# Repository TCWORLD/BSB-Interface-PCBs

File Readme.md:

# Boiler System Bus (BSB) Interface PCB Designs

This repository contains a series of PCB designs used to interface between the Boiler System Bus (BSB) of certain heating systems and network interfaces.

## MCU Software

The hardware is compatible with the ESP32 software implementations from [fredlcore/BSB-LAN](https://github.com/fredlcore/BSB-LAN/). 
Note: This repo is **not affiliated** with said project in any way - support queries for these PCB designs should **not** be directed to that project.

## Hardware

The hardware is based around an ESP32 controller, with either PoE LAN or WiFi network connectivity.

The PCBs have been laid out using Eagle PCB V6.6 and use predominantly surface mount components to make machine assembly easier. Parts used are all available for assembly in JLCPCBs parts catalogue.

A library file containing all parts used is included in the repository.

CAM files are included for generating 2-Layer and 4-Layer Gerber files using a naming scheme compatible with JLCs upload.

The repository contains a ULP file that can be run to generate the CPL/BOM files for upload to JLC. 
The `LCSC_PART` and `JLC_X/Y/ROTATION` attributes have been added for each component to simplify generation of the assembly spreadsheets required by JLC. If changing the PCB designs, ensure these attributes are updated as necessary.

### BSB-to-PoELaN for DIN Mount enclosure

A full implementation including ESP32 WROOM-32UE controller, PoE Ethernet power and networking, and USB programming and SD card interfaces.

This design has been built and is fully functional. It requires the following settings in the BSB-LAN software:

* In `BSB_LAN_config.h`: Configure the following setting:
    ```
    byte bus_pins[2] = {36,4};
    ```
* In `BSB_LAN_custom_setup.h`: Add the following code:
    ```
    // Set TX Enable pin to output and set high now that the system is initialised and the
    // TX line is being driven correctly
    pinMode(32, OUTPUT);
    digitalWrite(32, HIGH);
    ```

The board and components have been designed for use with JLCPCBs economic assembly process. 

The form factor of the board has been designed to fit in a Camdenboss CNMB/3/KIT DIN mount enclosure to provide a tidy fully enclosed solution.

### BSB-to-UEXT Daughter Board *UNTESTED*

Designed to work with the ESP32-POE-ISO controller from Olimex, connecting vial the UEXT headers.

The PCB schematic is simply based on the design found at in the GitHub repository [fredlcore/BSB-LAN](https://github.com/fredlcore/BSB-LAN/tree/master/BSB_LAN/schematics).

There are some slight adaptions to provide ESD protection for the isolated B2B interface and designed to be surface-mount machine for machine assembly. 

### BSB-to-WiFi for DIN Mount enclosure *UNTESTED*

A full implementation including ESP32 WROOM-32E controller, WiFi-only networking (PCB antenna, footprint compatible with external antenna), and USB programming and SD card interfaces.
This variant omits the LAN components to reduce the number of parts and make the board cheaper to manufacture. 
Power is supplied from either a 12V screw terminal (isolated through DC/DC for safety), or powered by the USB programming port.

The board and components have been designed for use with JLCPCBs economic assembly process. 

The form factor of the board has been designed to fit in a Camdenboss CNMB/2/KIT DIN mount enclosure to provide a tidy fully enclosed solution.

---

<br />This work is licensed under a <a rel="license" href="http://creativecommons.org/licenses/by-nc-sa/4.0/">Creative Commons Attribution-NonCommercial-ShareAlike 4.0 International License</a>.

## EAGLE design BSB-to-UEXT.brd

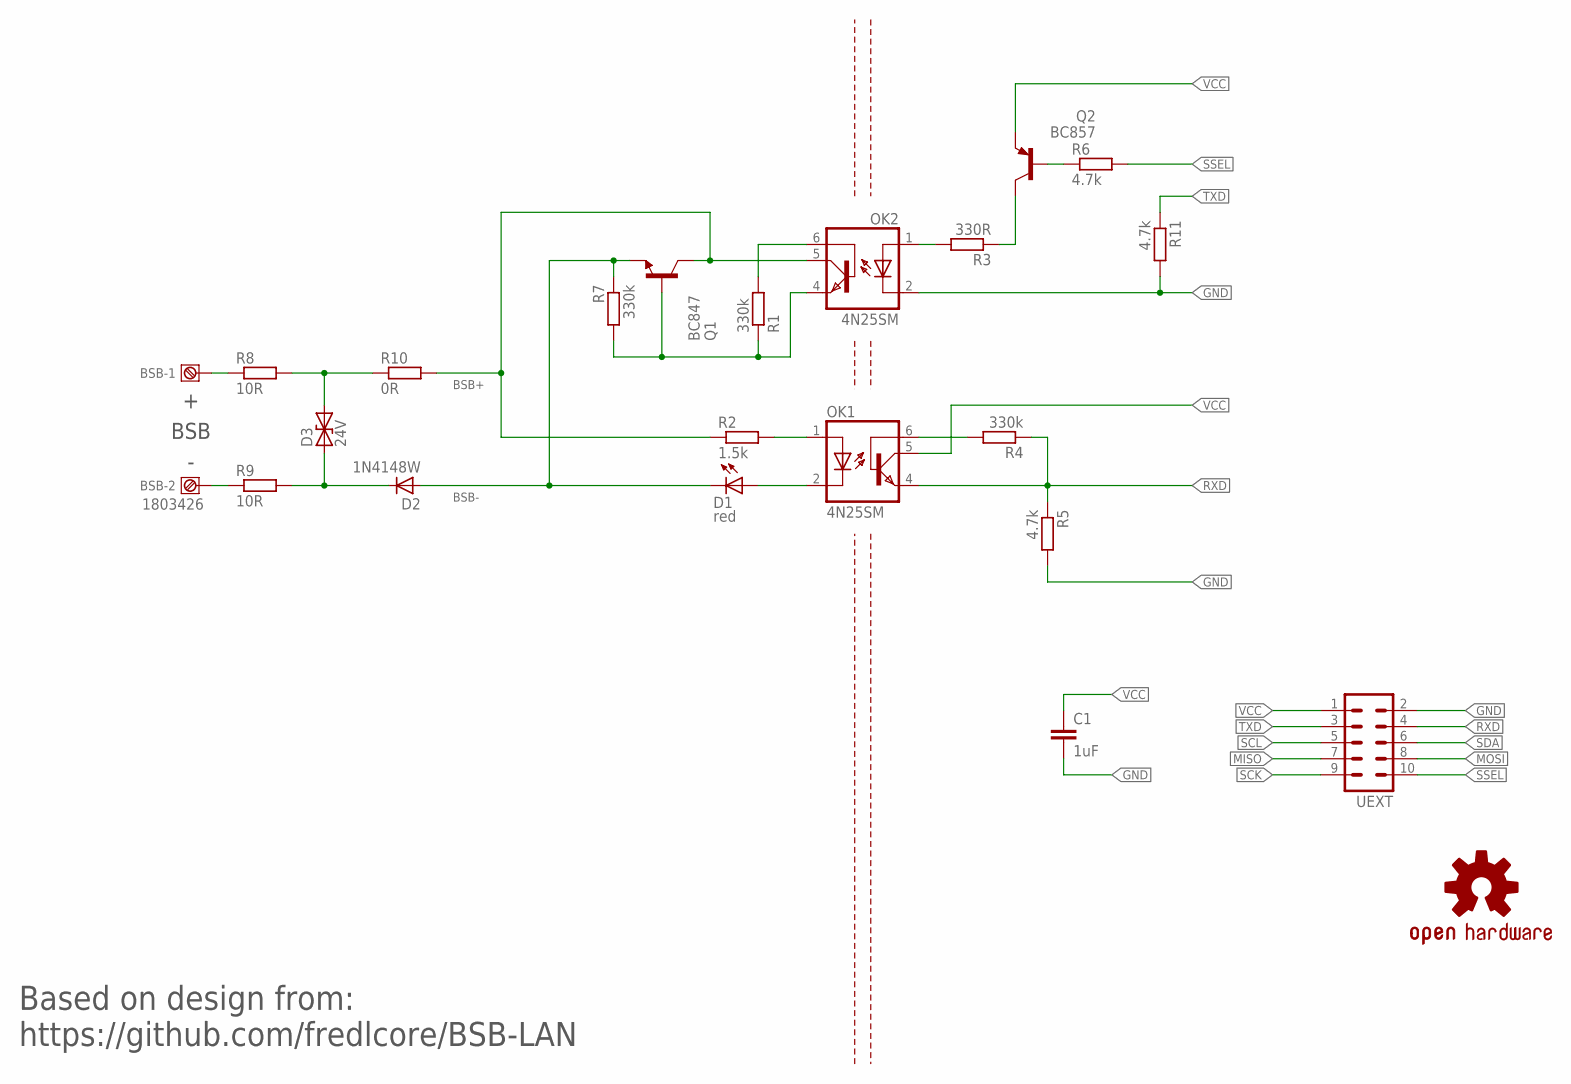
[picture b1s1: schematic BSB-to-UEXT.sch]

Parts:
BSB: 1803426; LCSC_PART C480514
C1: 1uF; C0805; LCSC_PART C28323
D1: red; CHIPLED_0805; LCSC_PART C84256
D2: 1N4148W; SOD123; LCSC_PART C81598
D3: 24V; SMBG; LCSC_PART C83268
OK1, OK2: 4N25SM; DIL6-SMD; LCSC_PART C258246
Q1: BC847; SOT23; LCSC_PART C130417
Q2: BC857; SOT23-BEC; LCSC_PART C426782
R1, R4, R7: 330k; R0805; LCSC_PART C17629
R2: 1.5k; R0805; LCSC_PART C4310
R3: 330R; R0805; LCSC_PART C17630
R5, R6, R11: 4.7k; R0805; LCSC_PART C17673
R8, R9: 10R; R1206; LCSC_PART C17903
R10: 0R; R1206L; LCSC_PART C17888
U$3: DNI; OSHW-LOGO-M
UEXT: ML10F

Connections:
BSB+: OK2.5 (COL), Q1.3 (C), R2.1, R10.2
BSB-: D1.C, D2.A, Q1.2 (E), R7.1
BSB-RX-A: OK1.1 (A), R2.2
BSB-RX-K: D1.A, OK1.2 (C)
BSB-TX-B: OK2.6 (BAS), R1.2
BSB-TX-E: OK2.4 (EMI), Q1.1 (B), R1.1, R7.2
CON-BSB+: BSB.1, R8.1
CON-BSB-: BSB.2, R9.1
GND: C1.2, OK2.2 (C), R5.2, R11.2, UEXT.2
MISO: UEXT.7
MOSI: UEXT.8
RXD: OK1.4 (EMI), R4.1, R5.1, UEXT.4
RXD-B: OK1.6 (BAS), R4.2
SCK: UEXT.9
SCL: UEXT.5
SDA: UEXT.6
SSEL: R6.2, UEXT.10
TVS-BSB+: D3.2, R8.2, R10.1
TVS-BSB-: D2.C, D3.1, R9.2
TXD: R11.1, UEXT.3
TXD-A: OK2.1 (A), R3.2
TXD-B: Q2.B, R6.1
TXD-C: Q2.C, R3.1
VCC: C1.1, OK1.5 (COL), Q2.E, UEXT.1

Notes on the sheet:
+ BSB -
Based on design from: https://github.com/fredlcore/BSB-LAN

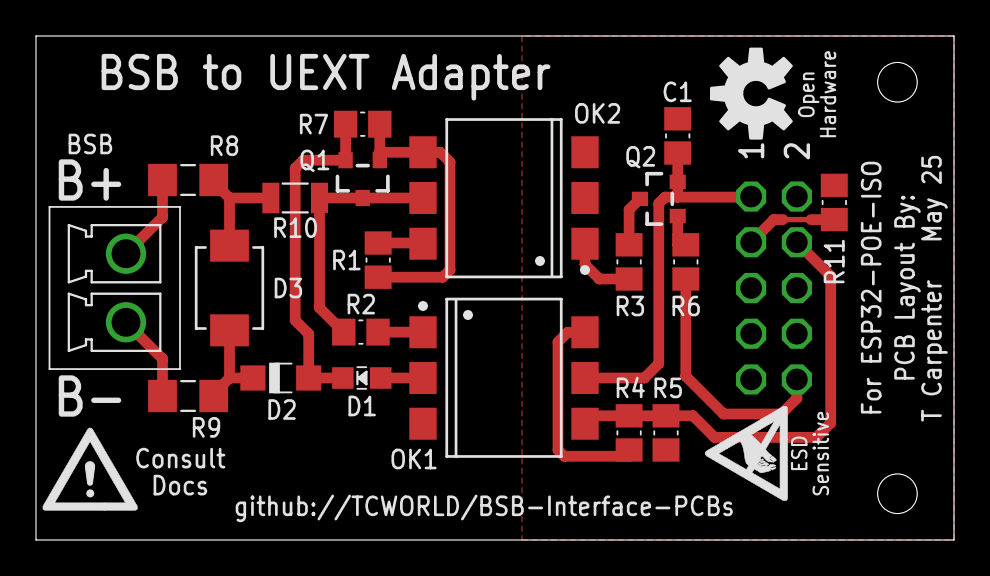
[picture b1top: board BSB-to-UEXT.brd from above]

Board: 2 copper layers, 51.0 x 28.0 mm, 24 parts (1 on the bottom side), 19 nets.

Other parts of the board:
U$1: WARN-TINY
U$2: ESD-TINY

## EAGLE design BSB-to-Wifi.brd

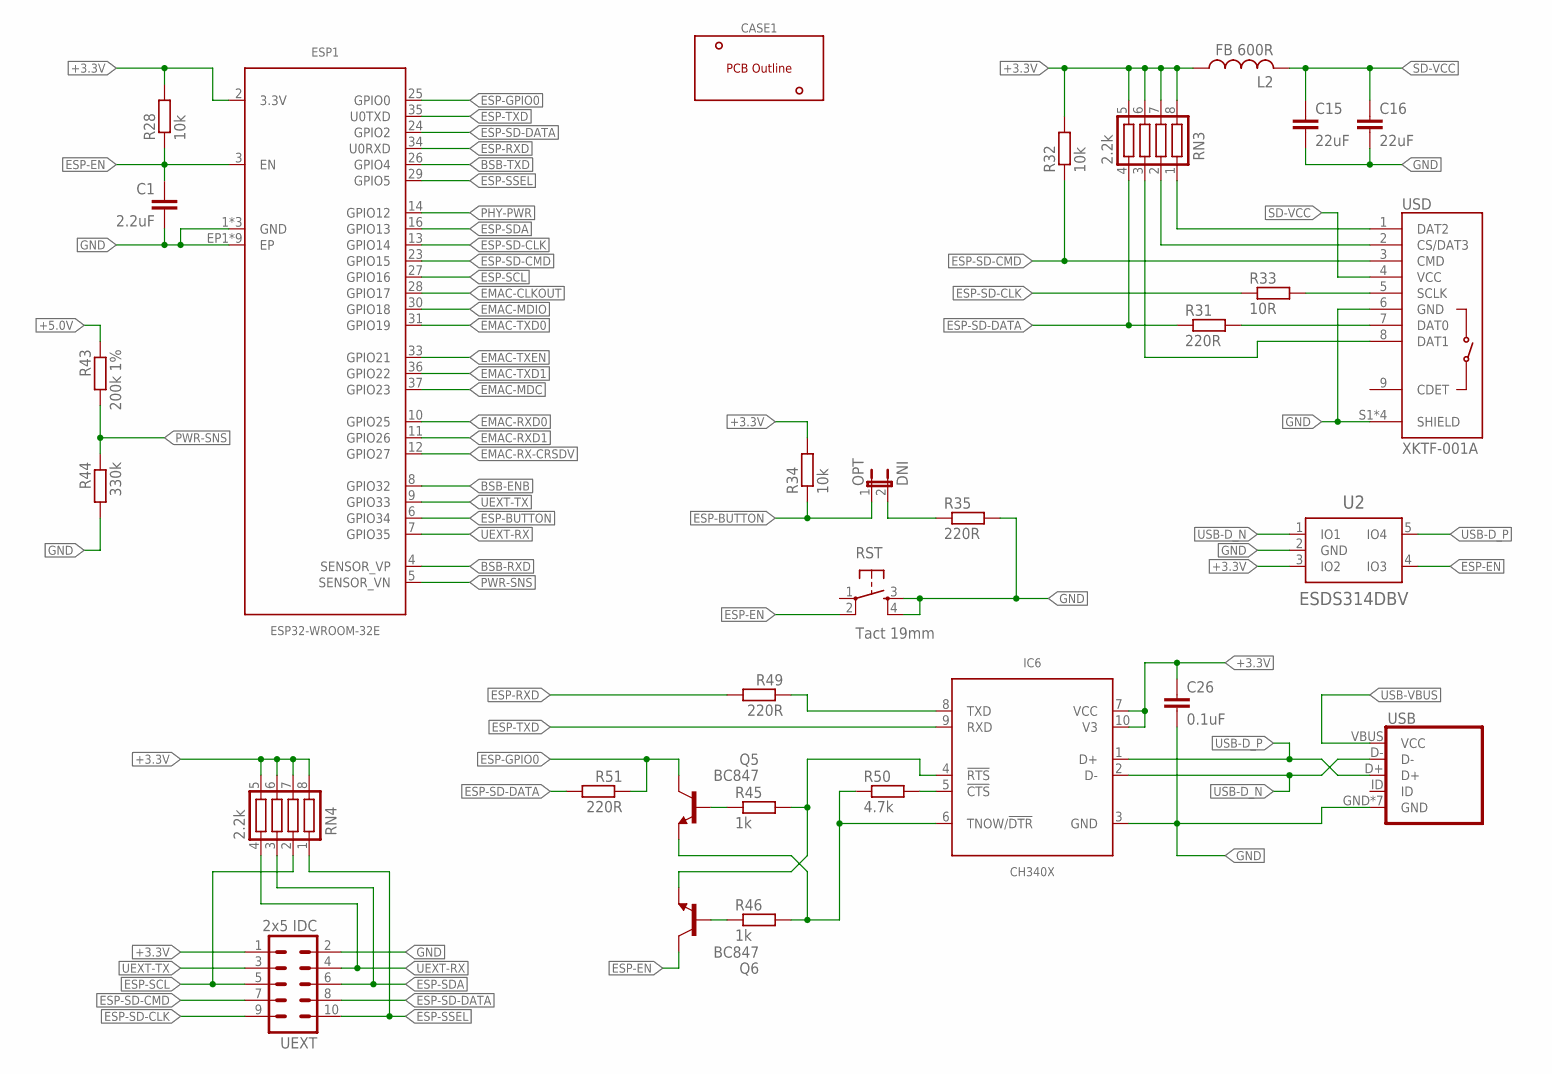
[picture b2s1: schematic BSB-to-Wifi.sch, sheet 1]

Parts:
C1: 2.2uF; C0603; LCSC_PART C23630
C15, C16: 22uF; C0805L; LCSC_PART C45783
C26: 0.1uF; C0402; LCSC_PART C1525
CASE1: DNI; CNMB/2-
ESP1: ESP32-WROOM-32E
IC6: CH340X; MSOP10
L2: FB 600R; L2010; LCSC_PART C1017
OPT: DNI; 1X02
Q5: BC847; SOT23; LCSC_PART C130417
Q6: BC847; SOT23
R28, R32, R34: 10k; R0402; LCSC_PART C25744
R31, R35, R49, R51: 220R; R0402; LCSC_PART C25091
R33: 10R; R0603L; LCSC_PART C22859
R43: 200k 1%; R0402; LCSC_PART C25764
R44: 330k; R0603L; LCSC_PART C23137
R45, R46: 1k; R0402; LCSC_PART C11702
R50: 4.7k; R0402; LCSC_PART C25900
RN3, RN4: 2.2k; CTS742C083; LCSC_PART C414564
RST: Tact 19mm; TACTILE_SWITCH; LCSC_PART C2837529
U2: ESDS314DBV; DBV0005A-SOT23
UEXT: 2x5 IDC; ML10
USB: ZX62-B-5PA(33); USB-MICROB
USD: XKTF-001A; MICRO-SD

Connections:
+3.3V: C26.1, ESP1.2 (3.3V), IC6.7 (VCC), IC6.10 (V3), L2.1, R28.2, R32.2, R34.2, RN3.5, RN3.6, RN3.7, RN3.8, RN4.5, RN4.6, RN4.7, RN4.8, U2.3 (IO2), UEXT.1; also elsewhere on the board
+5.0V: R43.1; also elsewhere on the board
BSB-ENB: ESP1.8 (GPIO32); also elsewhere on the board
BSB-RXD: ESP1.4 (SENSOR_VP); also elsewhere on the board
BSB-TXD: ESP1.26 (GPIO4); also elsewhere on the board
CH340-!CTS: IC6.5 (!CTS), R50.2
CH340-!DTR: IC6.6 (TNOW/!DTR), Q5.2 (E), R46.2, R50.1
CH340-!RTS: IC6.4 (!RTS), Q6.2 (E), R45.2
CH340-TXD: IC6.8 (TXD), R49.1
EMAC-CLKOUT: ESP1.28 (GPIO17)
EMAC-MDC: ESP1.37 (GPIO23)
EMAC-MDIO: ESP1.30 (GPIO18)
EMAC-RX-CRSDV: ESP1.12 (GPIO27)
EMAC-RXD0: ESP1.10 (GPIO25)
EMAC-RXD1: ESP1.11 (GPIO26)
EMAC-TXD0: ESP1.31 (GPIO19)
EMAC-TXD1: ESP1.36 (GPIO22)
EMAC-TXEN: ESP1.33 (GPIO21)
ESP-BUTTON: ESP1.6 (GPIO34), OPT.1, R34.1
ESP-BUTTON-R: OPT.2, R35.1
ESP-EN: C1.1, ESP1.3 (EN), Q6.3 (C), R28.1, RST.2, U2.4 (IO3)
ESP-EN-OE: Q6.1 (B), R46.1
ESP-GPIO0: ESP1.25 (GPIO0), Q5.3 (C), R51.1
ESP-GPIO0-OE: Q5.1 (B), R45.1
ESP-RXD: ESP1.34 (U0RXD), R49.2
ESP-SCL: ESP1.27 (GPIO16), RN4.2, UEXT.5
ESP-SD-CLK: ESP1.13 (GPIO14), R33.1, UEXT.9
ESP-SD-CMD: ESP1.23 (GPIO15), R32.1, UEXT.7, USD.3 (CMD)
ESP-SD-DATA: ESP1.24 (GPIO2), R31.1, R51.2, RN3.4, UEXT.8
ESP-SDA: ESP1.16 (GPIO13), RN4.3, UEXT.6
ESP-SSEL: ESP1.29 (GPIO5), RN4.1, UEXT.10
ESP-TXD: ESP1.35 (U0TXD), IC6.9 (RXD)
GND: C1.2, C15.2, C16.2, C26.2, ESP1.1 (GND), ESP1.15 (GND), ESP1.38 (GND), ESP1.EP1 (EP), ESP1.EP2 (EP), ESP1.EP3 (EP), ESP1.EP4 (EP), ESP1.EP5 (EP), ESP1.EP6 (EP), ESP1.EP7 (EP), ESP1.EP8 (EP), ESP1.EP9 (EP), IC6.3 (GND), R35.2, R44.2, RST.3, RST.4, U2.2 (GND), UEXT.2, USB.GND, USB.MT1 (GND), USB.MT2 (GND), USB.MT3 (GND), USB.MT4 (GND), USB.MT5 (GND), USB.MT6 (GND), USD.6 (GND), USD.S1 (SHIELD), USD.S2 (SHIELD), USD.S3 (SHIELD), USD.S4 (SHIELD); also elsewhere on the board
PHY-PWR: ESP1.14 (GPIO12)
PWR-SNS: ESP1.5 (SENSOR_VN), R43.2, R44.1
SD-DAT0: R31.2, USD.7 (DAT0)
SD-DAT1: RN3.3, USD.8 (DAT1)
SD-DAT2: RN3.1, USD.1 (DAT2)
SD-DAT3: RN3.2, USD.2 (CS/DAT3)
SD-SCLK: R33.2, USD.5 (SCLK)
SD-VCC: C15.1, C16.1, L2.2, USD.4 (VCC)
UEXT-RX: ESP1.7 (GPIO35), RN4.4, UEXT.4
UEXT-TX: ESP1.9 (GPIO33), UEXT.3
USB-D_N: IC6.2 (D-), U2.1 (IO1), USB.D-
USB-D_P: IC6.1 (D+), U2.5 (IO4), USB.D+
USB-VBUS: USB.VBUS (VCC); also elsewhere on the board

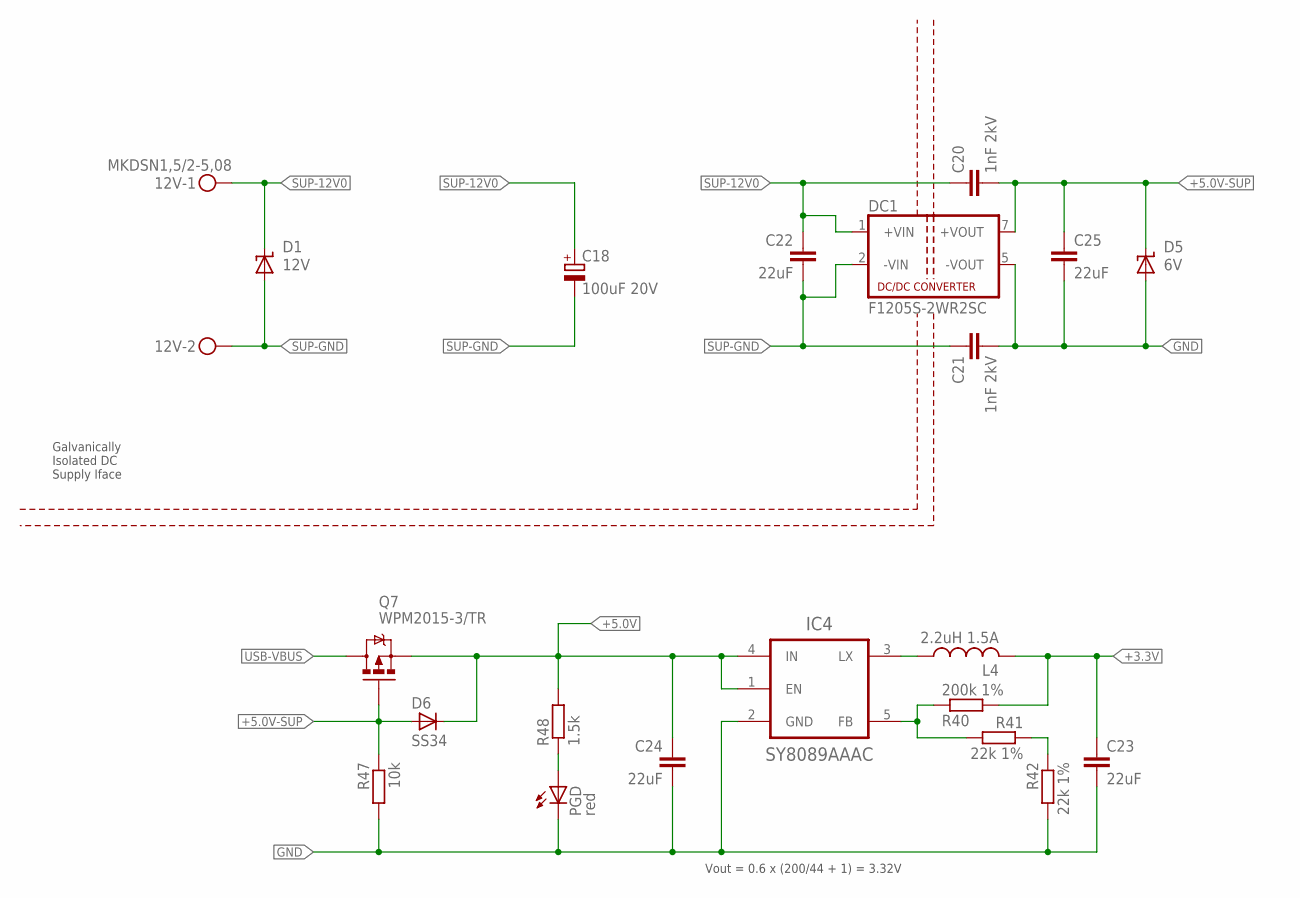
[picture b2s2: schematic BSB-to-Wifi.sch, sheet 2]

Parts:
12V: MKDSN1,5/2-5,08; MKDSN1_5-2-5_08
C18: 100uF 20V; SMC_D; LCSC_PART C7224
C20, C21: 1nF 2kV; C1206L; LCSC_PART C9196
C22, C23, C24, C25: 22uF; C0805; LCSC_PART C45783
D1: 12V; SMA; LCSC_PART C148213
D5: 6V; SMA; LCSC_PART C223993
D6: SS34; SMA; LCSC_PART C8678
DC1: F1205S-2WR2SC; SIP7-N
IC4: SY8089AAAC; DBV0005A-SOT23
L4: 2.2uH 1.5A; L4040P; LCSC_PART C135262
PGD: red; CHIP-LED0603; LCSC_PART C2286
Q7: WPM2015-3/TR; SOT23
R40: 200k 1%; R0402; LCSC_PART C25764
R41, R42: 22k 1%; R0402; LCSC_PART C25768
R47: 10k; R0402; LCSC_PART C25744
R48: 1.5k; R0603; LCSC_PART C22843

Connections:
3V3-FB: IC4.5 (FB), R40.1, R41.2
3V3-FB-RB: R41.1, R42.1
3V3-LX: IC4.3 (LX), L4.1
+3.3V: C23.1, L4.2, R40.2; also elsewhere on the board
+5.0V: C24.1, D6.C, IC4.1 (EN), IC4.4 (IN), Q7.2 (S), R48.2; also elsewhere on the board
+5.0V-SUP: C20.2, C25.1, D5.C, D6.A, DC1.7 (+VOUT), Q7.1 (G), R47.1
GND: C21.2, C23.2, C24.2, C25.2, D5.A, DC1.5 (-VOUT), IC4.2 (GND), PGD.C, R42.2, R47.2; also elsewhere on the board
PWR-LED: PGD.A, R48.1
SUP-12V0: 12V.1, C18.+, C20.1, C22.1, D1.C, DC1.1 (+VIN)
SUP-GND: 12V.2, C18.-, C21.1, C22.2, D1.A, DC1.2 (-VIN)
USB-VBUS: Q7.3 (D); also elsewhere on the board

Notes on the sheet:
Galvanically Isolated DC Supply Iface
Vout = 0.6 x (200/44 + 1) = 3.32V

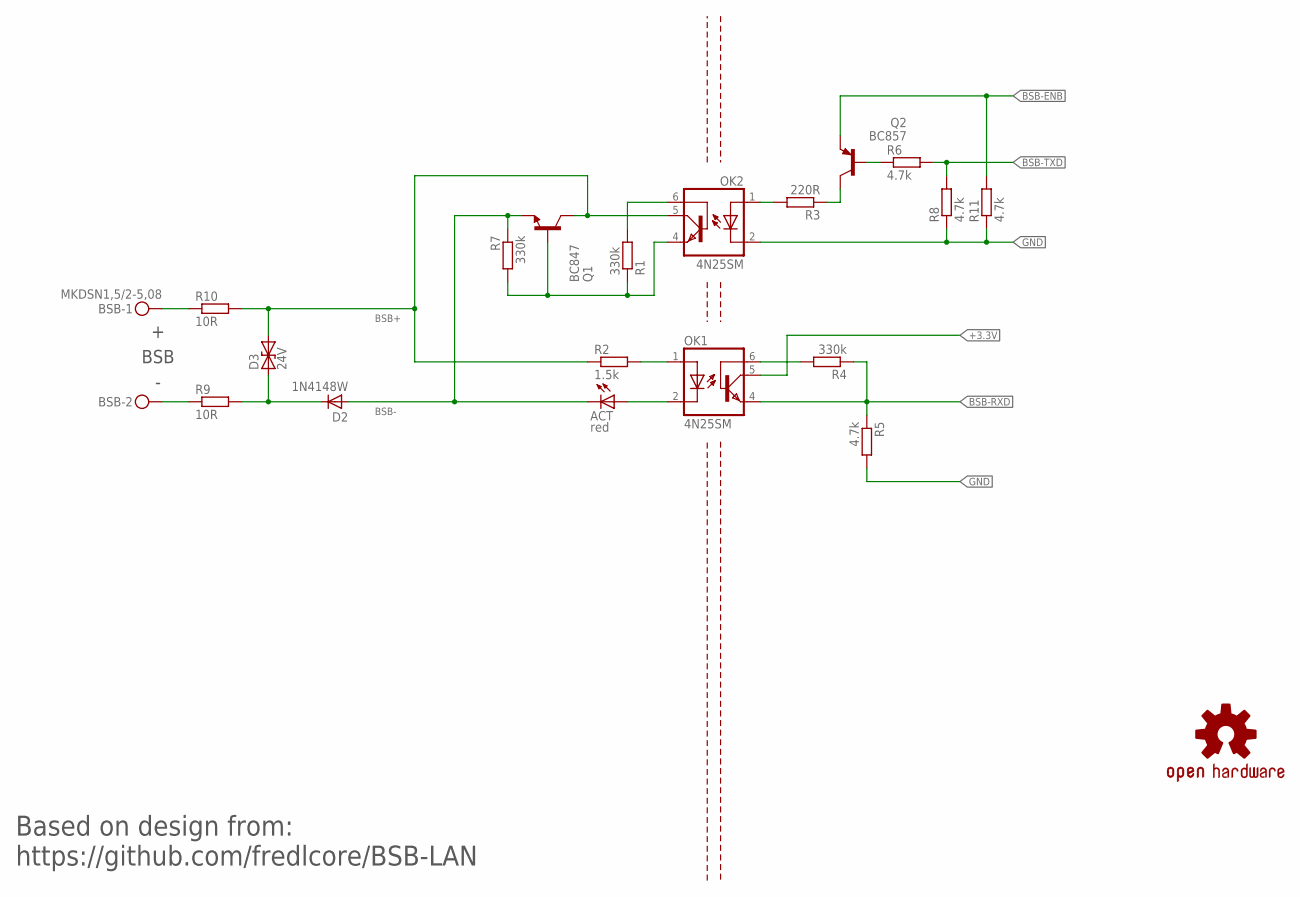
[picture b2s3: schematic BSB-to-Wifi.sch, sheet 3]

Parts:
ACT: red; CHIP-LED0603; LCSC_PART C2286
BSB: MKDSN1,5/2-5,08; MKDSN1_5-2-5_08
D2: 1N4148W; SOD123; LCSC_PART C81598
D3: 24V; SMBG; LCSC_PART C83268
OK1, OK2: 4N25SM; DIL6-SMD; LCSC_PART C258246
Q1: BC847; SOT23; LCSC_PART C130417
Q2: BC857; SOT23-BEC; LCSC_PART C426782
R1, R4, R7: 330k; R0603; LCSC_PART C23137
R2: 1.5k; R0603; LCSC_PART C22843
R3: 220R; R0402; LCSC_PART C25091
R5, R6, R8, R11: 4.7k; R0402; LCSC_PART C25900
R9, R10: 10R; R0603; LCSC_PART C22859
U$3: DNI; OSHW-LOGO-M

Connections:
+3.3V: OK1.5 (COL); also elsewhere on the board
BSB+: D3.2, OK2.5 (COL), Q1.3 (C), R2.1, R10.2
BSB-: ACT.C, D2.A, Q1.2 (E), R7.1
BSB-ENB: Q2.E, R11.2; also elsewhere on the board
BSB-RX-A: OK1.1 (A), R2.2
BSB-RX-K: ACT.A, OK1.2 (C)
BSB-RXD: OK1.4 (EMI), R4.1, R5.1; also elsewhere on the board
BSB-TX-B: OK2.6 (BAS), R1.2
BSB-TX-E: OK2.4 (EMI), Q1.1 (B), R1.1, R7.2
BSB-TXD: R6.2, R8.2; also elsewhere on the board
CON-BSB+: BSB.1, R10.1
CON-BSB-: BSB.2, R9.1
GND: OK2.2 (C), R5.2, R8.1, R11.1; also elsewhere on the board
RXD-B: OK1.6 (BAS), R4.2
TVS-BSB-: D2.C, D3.1, R9.2
TXD-A: OK2.1 (A), R3.2
TXD-B: Q2.B, R6.1
TXD-C: Q2.C, R3.1

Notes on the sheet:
+ BSB -
Based on design from: https://github.com/fredlcore/BSB-LAN

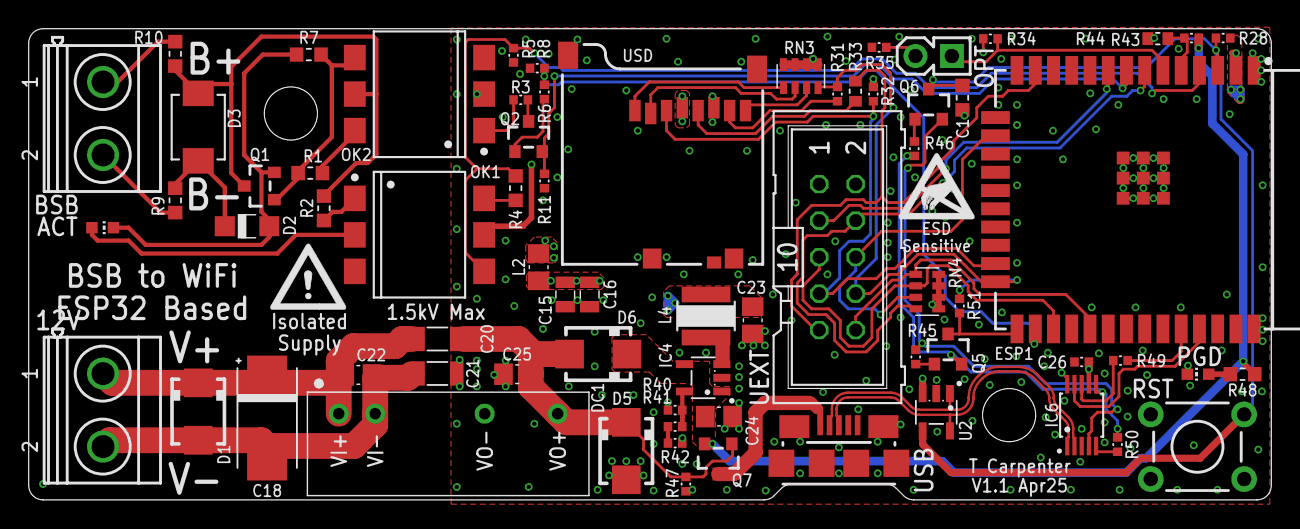
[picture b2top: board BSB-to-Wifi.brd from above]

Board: 4 copper layers, 86.5 x 32.8 mm, 74 parts (1 on the bottom side), 56 nets.

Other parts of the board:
U$1: WARN-TINY
U$2: ESD-TINY

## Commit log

2025-02-23 Initialise Repository with Readme etc.
2025-02-23 Initialise Eagle Project
2025-02-23 Implement First Draft Schematic/PCB Design
    Exported used library subset also included.
2025-03-01 Add OSHW Logo
2025-03-07 Add More Parts to BSB-LAN Library
    This includes basically sufficient parts to build an ESP32 dev kit.
2025-03-07 Begin designing full BSB-LAN + ESP32 Board
    Rather than a module that plugs onto an Olimex dev kit, this is a fully integrated board which includes the ESP32, PoE Ethernet, USB programming Iface. and BSB interface.
    The board is designed to fit into a DIN rail enclosure (Camdenboss CNMB/2).
2025-03-07 Correct uSD Card Footprint
    Add keepout zone for SD card
2025-03-07 Route LAN8710A connections on full PCB
2025-03-07 Add Keep-out to DIN enclosure footprint
    On the rear of the board, add a keep-out zone where the plastic support frame is located.
2025-03-07 Finish Routing Full Board
    Route the remaining BSB components, and also fix arrangement of parts on rear of the board which were encroaching the DIN frame keep-out.
2025-03-07 Improve EMAC Clock Routing
    Ensure contiguous ground plane underneath as it transitions across the top layer.
2025-03-07 Fix Silk
2025-03-07 Rename Connector Footprint
    Remove special characters
2025-03-08 Fix USB Position and Pinout UEXT 3/4
    1. Move the microUSB port inward so that it doesn't foul the enclosure.
    2. Pinout UEXT 3/4 to the spare GPIO pins 32/33. The correct two pins are in use by the BSB interface so they were previously left unconnected on UEXT, but we might as well have other GPIOs connected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
2025-03-08 Assign JLC Part Numbers
    Minor adaptions to available passive parts and packages and now all parts are available in JLCs inventory. LCSC_PART attributes have been applied to aid in BoM creation.
    Additionally add extra ESD protection for USB port.
2025-03-08 Generate 3D Rendering
2025-03-08 Update Git Ignore
    Ignore eagleUp generated files.
2025-03-08 Begin optimising for assembly cost
    Trying to reduce the number of different components, as well as instances where the same component is used on two sides of the board (incurs double assembly setup fee).
2025-03-08 Move LAN IC to Top Side
    With LAN IC on the top side, the board could be manufactered with only the top-side components populated, and with the exception of the uSD card all the bottom side parts are then relatively easy to 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
2025-03-08 Correct CNMB Footprint Keepout
    The zone was measured wrong from the model. Need the backside components to be further from the edge. Fix the board layout to achieve this.
2025-03-09 Add CNMB/3 Footprint and Update Libs
    Add footprint for the next size up enclosure.
2025-03-09 Route Single Sided Assembly Version
    Create a version of the full design that uses the wider CNMB/3/KIT enclosure. This gives enough space to place all components on the top layer which should significantly reduce assembly cost.
2025-03-09 Add CAM and ULP Helper Files
    For generating Gerber and BOM files.
2025-03-09 Fix RJ45 Position on Full-SS Board
    To ensure it's pins don't foul the PCB keepout zone.
2025-03-09 Correct PoE IC Part Number
    The LCSC_PART selected was the TPS2376DDA but the schematic value was TPS2375D, This actually has a slightly different footprint - the DDA has a thermal pad.
    Update to account for the change.
2025-03-09 Correct Component Rotation Values in JLC CPL
    Add rotation correction factors to parts which import in the wrong orientation.
2025-03-09 Reduce P1 Dot Side for DCDC
    Doesn't need to be 1mm!
2025-03-09 Change Stackup to JLC Default 4L
    Use the default stack-up using 7628 to allow the use of Economic assembly. Update trace widths of diff pairs accordingly.
2025-03-09 Add 3D Model of Full SS Design
2025-03-10 Fix CNMB/3 Terminal Positions
    And realign PCB components to the new coordinates. This is based on measurements of the 3D model in Solidworks.
    The ethernet connector has also been realigned to be central within three terminal blocks to make it easier to cut out its opening,
2025-03-11 Add Missing Pull-Up Resistors on I2C
2025-03-12 Correct Pinout of DC-DC Converter
    Not sure quite how I messed up the pin assignments that badly!
2025-03-12 Update 3D Models
2025-03-12 Correct LCSC_PART Attributes
    The power sense divider values were changed, but the attributes didn't get updated.
2025-03-12 Correct X-Y Offsets on some components for JLC CPL
    Four of the part origins in the design didn't match with the JLC CPL processor origins. Add extra attributes and modify ULP script to account for this.
2025-03-13 Create Wi-Fi Only Variant
    All PoE and Ethernet circuitry removed to make a lower cost more compact unit that uses Wi-Fi for comms.
    Runs from either a 12V supply or USB. The 12V supply is through an isolated DC-DC so could be sourced from the RVS21
2025-03-13 Update Libraries in basic BSB-LAN design
    Bring up to date with JLC export attributes.
2025-03-13 Add missing pull-down to BSB-LAN adapter
    4.7k on the TX pin to assist with boot issues on the Olimex dev kit.
2025-03-17 Add Missing LCSC_PART Attributes on BSB-LAN-Full-Wifi
    Missing TVS and DC-DC JLC assembly part numbers.
2025-03-17 Reduce Wifi BoM Complexity
    There were some weird values left that were holdovers from the LAN board where they were used elsewhere.
2025-03-25 Annotate Alternate Parts for Full S-S design
    Some parts can have alternative compatible PNs.
2025-04-14 Correct JLC SMT Export Script
    1. Fix modulo function. The divisor should be removed if the value is equal to it (i.e. a value of 360 with divisor of 360 should become 0).
    2. Correct position offsetting on bottom layer. Need to account for the flip.
2025-04-14 Library Improvements
    1. Add JLC X-Y correction to ESP32 w/ external antenna, and the right angled reset switch.
    2. Fix hole positions for SIP7 DC-DC package.
    3. Correct hole sizes for Camdenboss enclosures. Should be 6-32 UNC not M3. Restrict is set for smaller button head screws.
2025-04-14 Correct ESP32 Prog Control + Update Libraries
    1. Correct the control of automatic bootloader entry by adding missing resistor from GPIO2 to GPIO0.
    2. Update libraries and fix layout to account for changes.
    3. Change the LAN versions of the boards to use the ESP32 with external antenna. If the PCB antenna is used then it is not possible to get the PCB into the enclosure because components stick out on b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
2025-04-17 Smaller Reset Switch on BSB-LAN-Full
    Use a smaller reset switch so that it is mechanically possible to fit the board into its enclosure - we can't have components hanging over both ends of the board otherwise it won't fit into the case.
2025-04-17 Tweak LAN Connector Location on BSB-LAN-Full-SS
    Improve shield ground plane connectivity.
2025-04-19 Adjust Silkscreen
2025-04-19 Rearrange Repository Files
2025-04-19 Update Eagle Project File Descriptions
2025-04-19 Update BSB-to-PoELAN 3D Model
2025-05-08 Add BSB Tx Enable Control
    Move the UEXT RX on GPIO35 (input only), and use GPIO32 instead for controlling whether the BSB-TXD pin can drive the optocoupler. This basically replaces the +3.3V connection on the emitter of the i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
    What this means is that when the ESP32 has not yet booted, or if it crashes along the way, the BSB bus is not being driven into TX mode by the pull-down bootstrap resistor. This should stop BSB bus s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
    This will require custom code in the BSB firmware setup (BSB_LAN_custom_setup.h) to configure the enable pin to be an output and driven high. Until that is done the BSB bus remai
2025-05-08 Change BSB-to-UEXT Tx Pin Assignment
    Follow the BSB-LAN repo in moving TX onto the UEXT-SSEL pin instead of the UEXT-TX pin. This is done to avoid issues with the TX pin needing to be pulled low during the boot phase, but that in turn w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
2025-05-20 Update Readme.md
    The `BSB-to-PoELAN` board has now been testing and works correctly.
    Add the required config settings into the readme.
